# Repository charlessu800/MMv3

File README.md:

# MMv3

MMv3 is the 3rd generation robot platform used to teach the IEEE Micromouse DeCal at UC Berkeley. It was designed with usability, manufacturability, size, and cost in mind.

## Schedule

Skeleton lab code, lab documents, and solutions are stored in [labs/](labs/), [docs/](docs/), and [solutions/](solutions/), respectively. To get started with a lab, simply copy the contents of the folder over to the CircuitPython drive and edit files from there.

* [lab1](docs/lab1.md) - CircuitPython Basics
* [lab2](docs/lab2.md) - Assembly
* [sanity](docs/sanity.md) - Hardware Check
* [lab3](docs/lab3.md) - Encoders
* [lab4](docs/lab4.md) - IR Sensors
* [lab5](docs/lab5.md) - Odometry and Motor Control
* **Checkpoint 1**: Does your mouse drive?
* [lab6](docs/lab6.md) - Intro to PID
* [lab7](docs/lab7.md) - More PID
* **Checkpoint 2**: Does your mouse straight under PID control?
* [lab8](docs/lab8.md) - Maze Solving Primitives **(WIP)**

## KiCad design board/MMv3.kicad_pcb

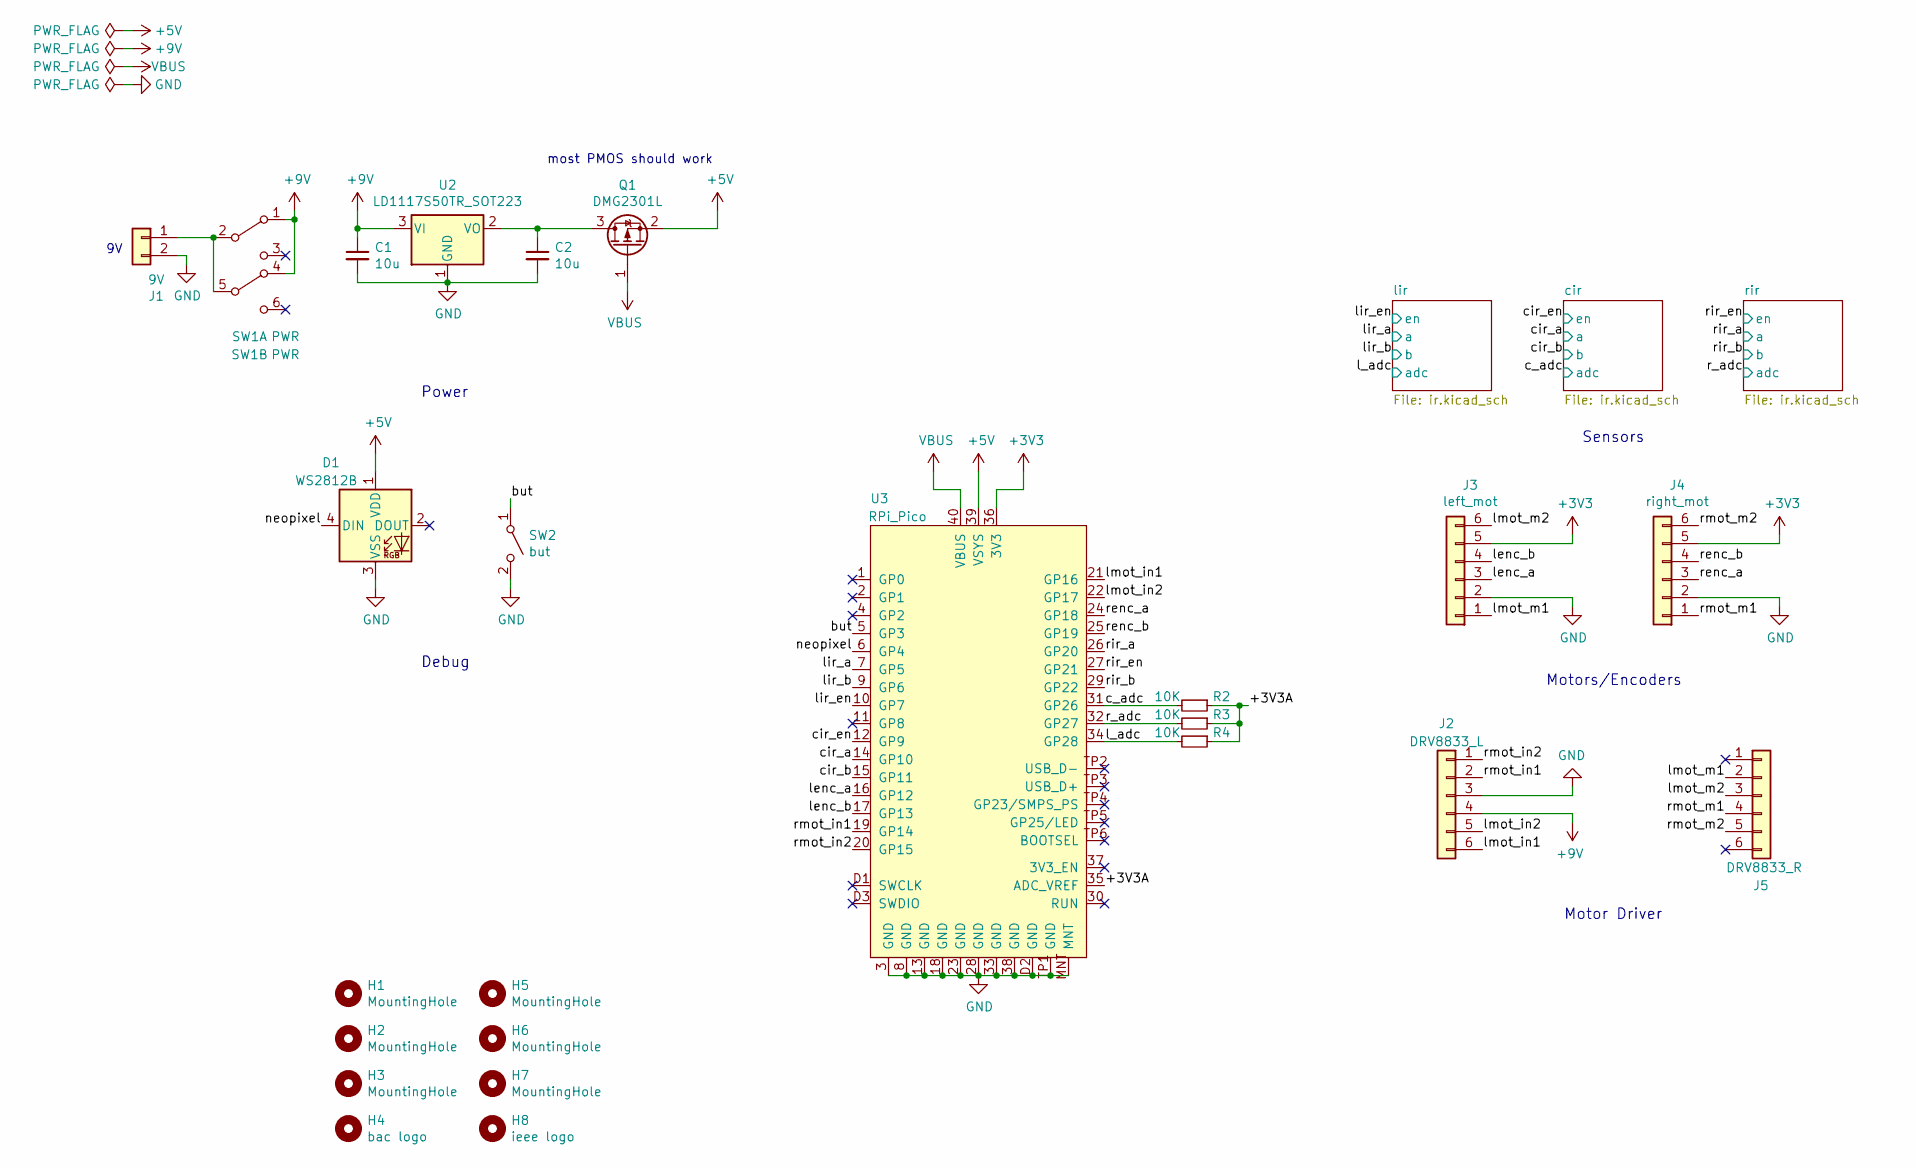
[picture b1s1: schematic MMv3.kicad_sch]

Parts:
C1, C2: 10u; C_0805_2012Metric
D1: WS2812B; LED_WS2812B_PLCC4_5.0x5.0mm_P3.2mm
H1, H2, H3, H5, H6, H7: MountingHole; MountingHole_3.2mm_M3_Pad_TopBottom
H4: bac logo; bac_logo
H8: ieee logo; ieee_logo
J1: 9V; Keystone_593_594
J2: DRV8833_L; PinSocket_1x06_P2.54mm_Vertical
J3: left_mot; JST_ZH_Vert_6pin
J4: right_mot; JST_ZH_Vert_6pin
J5: DRV8833_R; PinSocket_1x06_P2.54mm_Vertical
Q1: DMG2301L; SOT-23
R2, R3, R4: 10K; R_0805_2012Metric
SW1: PWR; SW_CuK_JS202011CQN_DPDT_Straight
SW2: but; SWDIP2_256X170P100
U2: LD1117S50TR_SOT223; SOT-223-3_TabPin2
U3: RPi_Pico; RPi_Pico_SMD

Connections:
+3V3: J3.5, J4.5, U3.36 (3V3)
+5V: D1.1 (VDD), Q1.2 (S), U3.39 (VSYS); also elsewhere on the board
+9V: C1.1, J2.4, SW1.1 (A), SW1.4 (A), U2.3 (VI)
/+3V3A: R2.1, R3.1, R4.1, U3.35 (ADC_VREF)
/but: SW2.1 (A), U3.5 (GP3)
/c_adc: R2.2, U3.31 (GP26); also elsewhere on the board
/cir_a: U3.14 (GP10); also elsewhere on the board
/cir_b: U3.15 (GP11); also elsewhere on the board
/cir_en: U3.12 (GP9); also elsewhere on the board
/l_adc: R4.2, U3.34 (GP28); also elsewhere on the board
/lenc_a: J3.3, U3.16 (GP12)
/lenc_b: J3.4, U3.17 (GP13)
/lir_a: U3.7 (GP5); also elsewhere on the board
/lir_b: U3.9 (GP6); also elsewhere on the board
/lir_en: U3.10 (GP7); also elsewhere on the board
/lmot_in1: J2.6, U3.21 (GP16)
/lmot_in2: J2.5, U3.22 (GP17)
/lmot_m1: J3.1, J5.2
/lmot_m2: J3.6, J5.3
/neopixel: D1.4 (DIN), U3.6 (GP4)
/r_adc: R3.2, U3.32 (GP27); also elsewhere on the board
/renc_a: J4.3, U3.24 (GP18)
/renc_b: J4.4, U3.25 (GP19)
/rir_a: U3.26 (GP20); also elsewhere on the board
/rir_b: U3.29 (GP22); also elsewhere on the board
/rir_en: U3.27 (GP21); also elsewhere on the board
/rmot_in1: J2.2, U3.19 (GP14)
/rmot_in2: J2.1, U3.20 (GP15)
/rmot_m1: J4.1, J5.4
/rmot_m2: J4.6, J5.5
GND: C1.2, C2.2, D1.3 (VSS), J1.2, J2.3, J3.2, J4.2, SW2.2 (B), U2.1 (GND), U3.3 (GND), U3.8 (GND), U3.13 (GND), U3.18 (GND), U3.23 (GND), U3.28 (GND), U3.33 (GND), U3.38 (GND), U3.D2 (GND), U3.MNT, U3.TP1 (GND); also elsewhere on the board
unnamed: J1.1, SW1.2 (B), SW1.5 (B)
unnamed: C2.1, Q1.3 (D), U2.2 (VO)
VBUS: Q1.1 (G), U3.40 (VBUS)

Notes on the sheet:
Motor Driver
Sensors
Power
Motors/Encoders
most PMOS should work
Debug

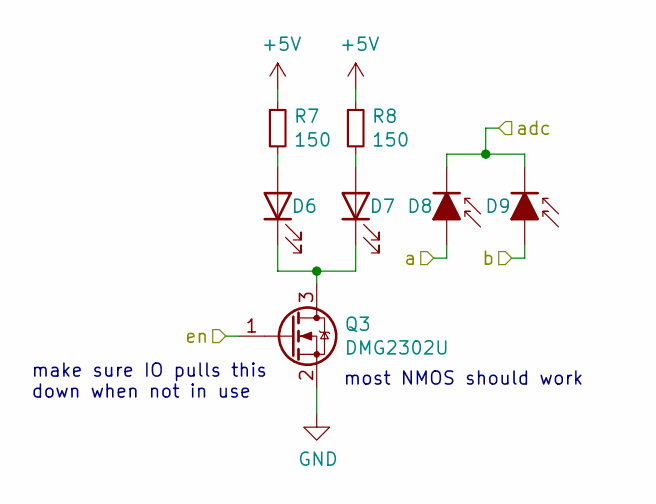
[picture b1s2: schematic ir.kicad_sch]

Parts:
D6, D7: LED; LED_D3.0mm_RH_THT_Clear
D8, D9: D_Photo_ALT; LED_D3.0mm_RH_THT_IRBlack
Q3: DMG2302U; SOT-23
R7, R8: 150; R_0805_2012Metric

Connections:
+5V: R7.1, R8.1; also elsewhere on the board
/c_adc: D8.1 (K), D9.1 (K); also elsewhere on the board
/cir_a: D8.2 (A); also elsewhere on the board
/cir_b: D9.2 (A); also elsewhere on the board
/cir_en: Q3.1 (G); also elsewhere on the board
GND: Q3.2 (S); also elsewhere on the board
unnamed: D6.2 (A), R7.2
unnamed: D6.1 (K), D7.1 (K), Q3.3 (D)
unnamed: D7.2 (A), R8.2

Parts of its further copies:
D2, D3, D10, D11: LED; LED_D3.0mm_RH_THT_Clear
D4, D5, D12, D13: D_Photo_ALT; LED_D3.0mm_RH_THT_IRBlack
Q2, Q4: DMG2302U; SOT-23
R5, R6, R9, R10: 150; R_0805_2012Metric

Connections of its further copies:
+5V: R5.1, R6.1, R9.1, R10.1; also elsewhere on the board
/l_adc: D4.1 (K), D5.1 (K); also elsewhere on the board
/lir_a: D4.2 (A); also elsewhere on the board
/lir_b: D5.2 (A); also elsewhere on the board
/lir_en: Q2.1 (G); also elsewhere on the board
/r_adc: D12.1 (K), D13.1 (K); also elsewhere on the board
/rir_a: D12.2 (A); also elsewhere on the board
/rir_b: D13.2 (A); also elsewhere on the board
/rir_en: Q4.1 (G); also elsewhere on the board
GND: Q2.2 (S), Q4.2 (S); also elsewhere on the board
unnamed: D2.2 (A), R5.2
unnamed: D2.1 (K), D3.1 (K), Q2.3 (D)
unnamed: D3.2 (A), R6.2
unnamed: D10.2 (A), R9.2
unnamed: D10.1 (K), D11.1 (K), Q4.3 (D)
unnamed: D11.2 (A), R10.2

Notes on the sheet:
make sure IO pulls this down when not in use
most NMOS should work

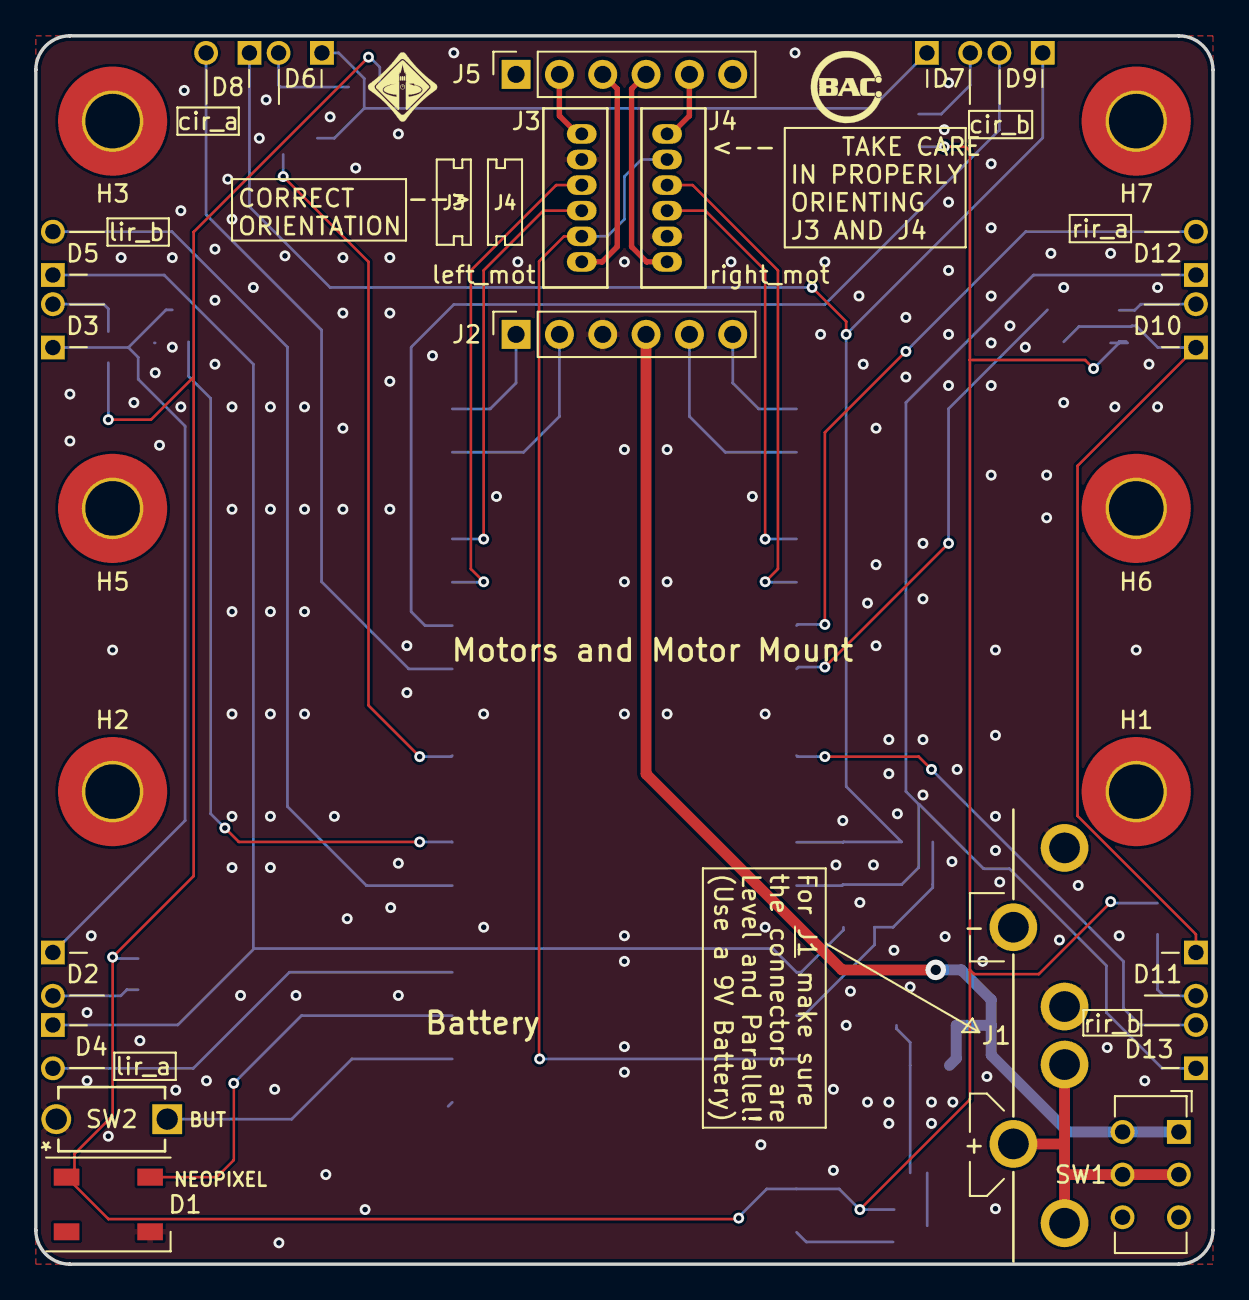
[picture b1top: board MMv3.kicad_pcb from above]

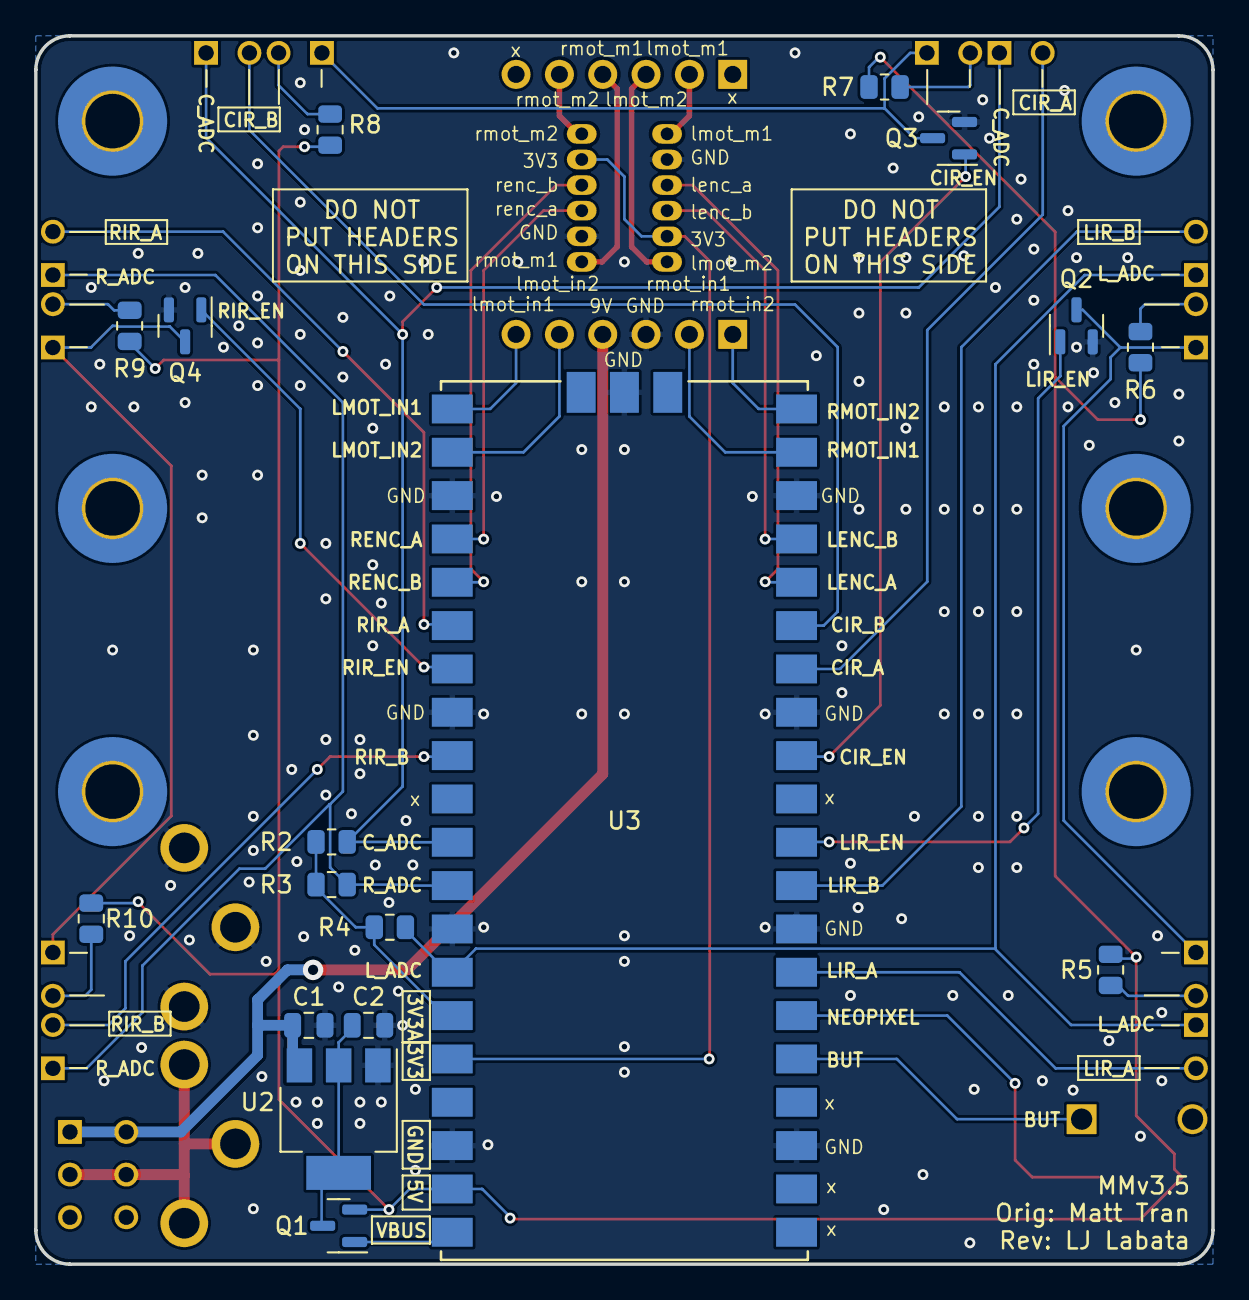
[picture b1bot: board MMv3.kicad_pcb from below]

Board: 2 copper layers, 69.0 x 72.0 mm, 45 parts (17 on the bottom side), 43 nets.

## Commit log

2024-11-05 Update firmware download
2024-11-05 Fixing firmware link
2024-11-05 Fixing firmware download hyperlink for good
2025-02-22 First Merge of IR and Encoder
    Changed around lab names for IR and Encoder (3->4) and file names overall (when the merge happens we will get rid of the original labs). Adjusted the IR lab to be more informational than menial.
2025-02-27 update sanity
2025-02-27 typo
2025-02-27 add clarity
2025-03-04 Update lab3.md
    changed name
2025-03-04 Rename lab3.md to lab4_0.md
2025-03-04 Rename lab4.md to lab3.md
2025-03-04 Rename lab4_0.md to lab4.md
2025-03-11 Update lab3.md
    clarity
2025-03-11 Update lab3.md
    s
2025-03-11 Update lab4.md
    lot o' clarity
2025-03-11 THIS FILE USED TO BE NAMED constants.py
2025-03-11 Update lab4.md
    desc
2025-03-18 Update lab4.md to include our newly added code
2025-03-18 grammar lab4.md
2025-03-18 Provide students with more examples than TODOs
2025-04-16 Rename checkoff.md to checkoff.md
2025-04-23 Create lab PID
2025-04-23 Rename solutions/lab 5(PID) to solutions/lab 5.5/checkoff.md
2025-04-23 Rename solutions/lab5/checkoff.md to solutions/lab 5(PID)
2025-10-06 Clarify windows
2025-10-06 Clarity
2025-10-06 heehehehehehhe
2025-10-06 01001000 01100101 01101100 01101100 01101111
2025-10-14 Added more hints to lab4.md. DigitalInOut
2025-10-21 Created really rough draft of a troubleshotting doc
2025-10-22 Added dimensions to pcb and also printed out a pdf of the dimensions
2025-10-23 Incomplete debugging changes to lab 2
2025-10-23 Fixed the ordering of when to assemble motors
2025-10-30 Cleaned up the files in the solutions folder.
2025-10-30 Renamed lab 4 folder to lab4
2025-10-30 Trying to fix latex markdown formatting
2025-10-30 Fix formatting of K_p equations in checkoff.md for consistency Again
2025-10-30 Better formtatting for lab 6
2025-10-30 changing name of lab 6 markdown doc
2025-10-30 Update names for better legitbility
2025-10-30 Brevity and explanations
2025-10-30 Mouse go zoooom
2025-10-30 mouse go zooom
2025-11-03 Mouse go z
2025-11-03 mouse goo zoooom
2025-11-03 mouse still goes zoom
2025-11-04 mouse go vroooom
2025-12-19 Added 3D .step model of Pi Pico and whatever other settings and changes I forgot
2025-12-24 Finished silkscreen and moving components
2025-12-24 Changed silkscreen from 3.4 to 3.5
2025-12-24 Beginning 9V Battery LED indicator schematic circuit
2025-12-28 idk?
2025-12-31 first time running through instantDFM
2026-01-06 finished mmv3_5 now bought
2026-01-23 trying new markdown for picture captions
2026-01-23 fixed height fix
2026-01-23 checking if this is much better
2026-01-23 trying table
2026-01-23 table don't work
2026-01-23 span works!
2026-01-23 centered
2026-01-23 center figures wahhh?
2026-01-23 what?
2026-01-23 checking this works
2026-01-23 testing
2026-01-24 9.x is bad!
2026-01-24 Update CircuitPython library download instructions
2026-01-24 add images and update sanity documentation for clarity
2026-01-24 Enhance user prompts for clarity in main execution flow
2026-01-26 Added reflow soldering guide
2026-02-03 added ibom
2026-02-09 finished adding changes and updates to lab2 assembly
2026-02-09 testing interactive click box
2026-02-09 fixes
2026-02-09 smaller
2026-02-09 slight big neopixel
2026-02-09 trying zip in sanity
2026-02-09 adding zip file
2026-02-09 changed sanity.zip file name and fixed ibom download link
2026-02-09 finished editing sanity need to still add vscode extension documentation. not even tried editing troubleshooting
2026-02-09 grammar
2026-02-09 more grammar and notes for stuff to add
2026-02-09 more grammar
2026-02-09 glasses ppe warning
2026-02-10 Update sanity to include more mac context
2026-02-10 Add files for VScode serial monitor
2026-02-10 Update sanity.md to include VScode extension instructions
2026-02-10 Update sanity.md change size
